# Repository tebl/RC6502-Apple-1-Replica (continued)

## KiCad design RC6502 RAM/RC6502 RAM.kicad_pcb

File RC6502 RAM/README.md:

# RC6502 RAM

The original Apple 1 computer only came with 8KB of RAM (Random Access Memory), this was divided into two separate 4KB blocks and should match the following layout (picture from Tom Owads Apple 1 Replica book):

.PNG)

The RC6502 computer makes the same changes to the hardware dealing with RAM as was details in the previously mentioned book, the updated memory map should now match the one included below (note that any optional modules are not included here). The blue areas designating RAM have shifted positions, mostly we've moved the area usually used for Integer Basic into ROM (see the [ROM](https://github.com/tebl/RC6502/tree/master/RC6502%20ROM)-module for more information). The initial version of the RAM module simply split the 64K memory space supported by the 6502 processor into two, the lower 32K being dedicated to RAM giving us the following memory layout:

.PNG)

The newly redesigned RAM module now also support ROM ICs, this can be done by jumpering WE across pins 2-3 to disable the write signal usually sent to the chip. The previous scheme of splitting the memory space into two 32K sections has been kept, the HI/LO jumper is used as to select adressing segments between $0000 through $7FFF or alternatively $8000 through $FFFF. Each 4KB section within the selected 32KB segment can then be enabled/disabled using the corresponding jumpers, this way a single board can be active within memory segments of sizes from 4KB to 32KB.

When used in combination with (E)EPROMs smaller than 32KB, such as the 27C64 or 28C64 you need to leave A13_EN and A14_EN unjumpered since those pins would be designated NC (No Connect) on the ICs themselves. Note that since ICs of this size are usually 8KB you'd only have two 4KB blocks available, enabling these in the certain combinations would lead to repetitions within the memory space. 32KB ROM chips are more than likely cheaper to obtain anyway, meaning that this would be a nice way to add more ROM-based software to the computer without much added complexity.

# Schematic
The supplied KiCad files should be sufficient as both a schematic and as a starting
point for ordering PCBs, the schematic is also available in
[PDF-format](https://github.com/tebl/RC6502-Apple-1-Replica/blob/master/RC6502%20RAM/export/RC6502%20RAM.pdf). You can refer to the BOM below for a list of suggested components to use, part numbers in parenthesis are optional and is not required.

# BOM
These are the components needed to put together your very own RAM-module for the RC6502 computer, should be able to get all of this from your favourite parts supplier through your favourite local parts supplier. For the pin headers, both male and female - if you can't find the exact pin count, just buy the longer versions and snip/cut off the parts you don't need (get extra in case of accidents, and don't cut yourself either!). Part counts in parenthesis are to be considered optional, so if you don't have any plans for them - then they can probably be left out until you need them.

| Reference | Item                                  | Count  |
| --------- | ------------------------------------- | ------ |
| PCB       | Fabricate yourself using KiCad files  |     1  |
| C1-C5     | 100nF ceramic capacitor               |     5  |
| J3        | 1x39 right angle pin header, male     |     1  |
| JP1-JP2   | 1x2 straight pin header, male         |     2  |
| JP3-JP13  | 1x3 straight pin header, male         |    10  |
| U1        | 62256 SRAM or 28C256, both DIP-28     |     1  |
| U2        | 74LS138 DIP                           |     1  |
| U3-U4     | 74LS08 DIP                            |     2  |
| U5        | 74LS00 DIP                            |     1  |
|           | Jumper caps                           | 3 (10) |

If you would like to have a copy of one or more modules, what you'll need to do is zip up the contents of the export directory for each module and give that to your favourite PCB fabrication plant. Personally I prefer to use [PCBWay](https://www.pcbway.com/setinvite.aspx?inviteid=88707), each module has been designed to fit inside the 5$ dimensions. Use the link provided when signing up to support this project!

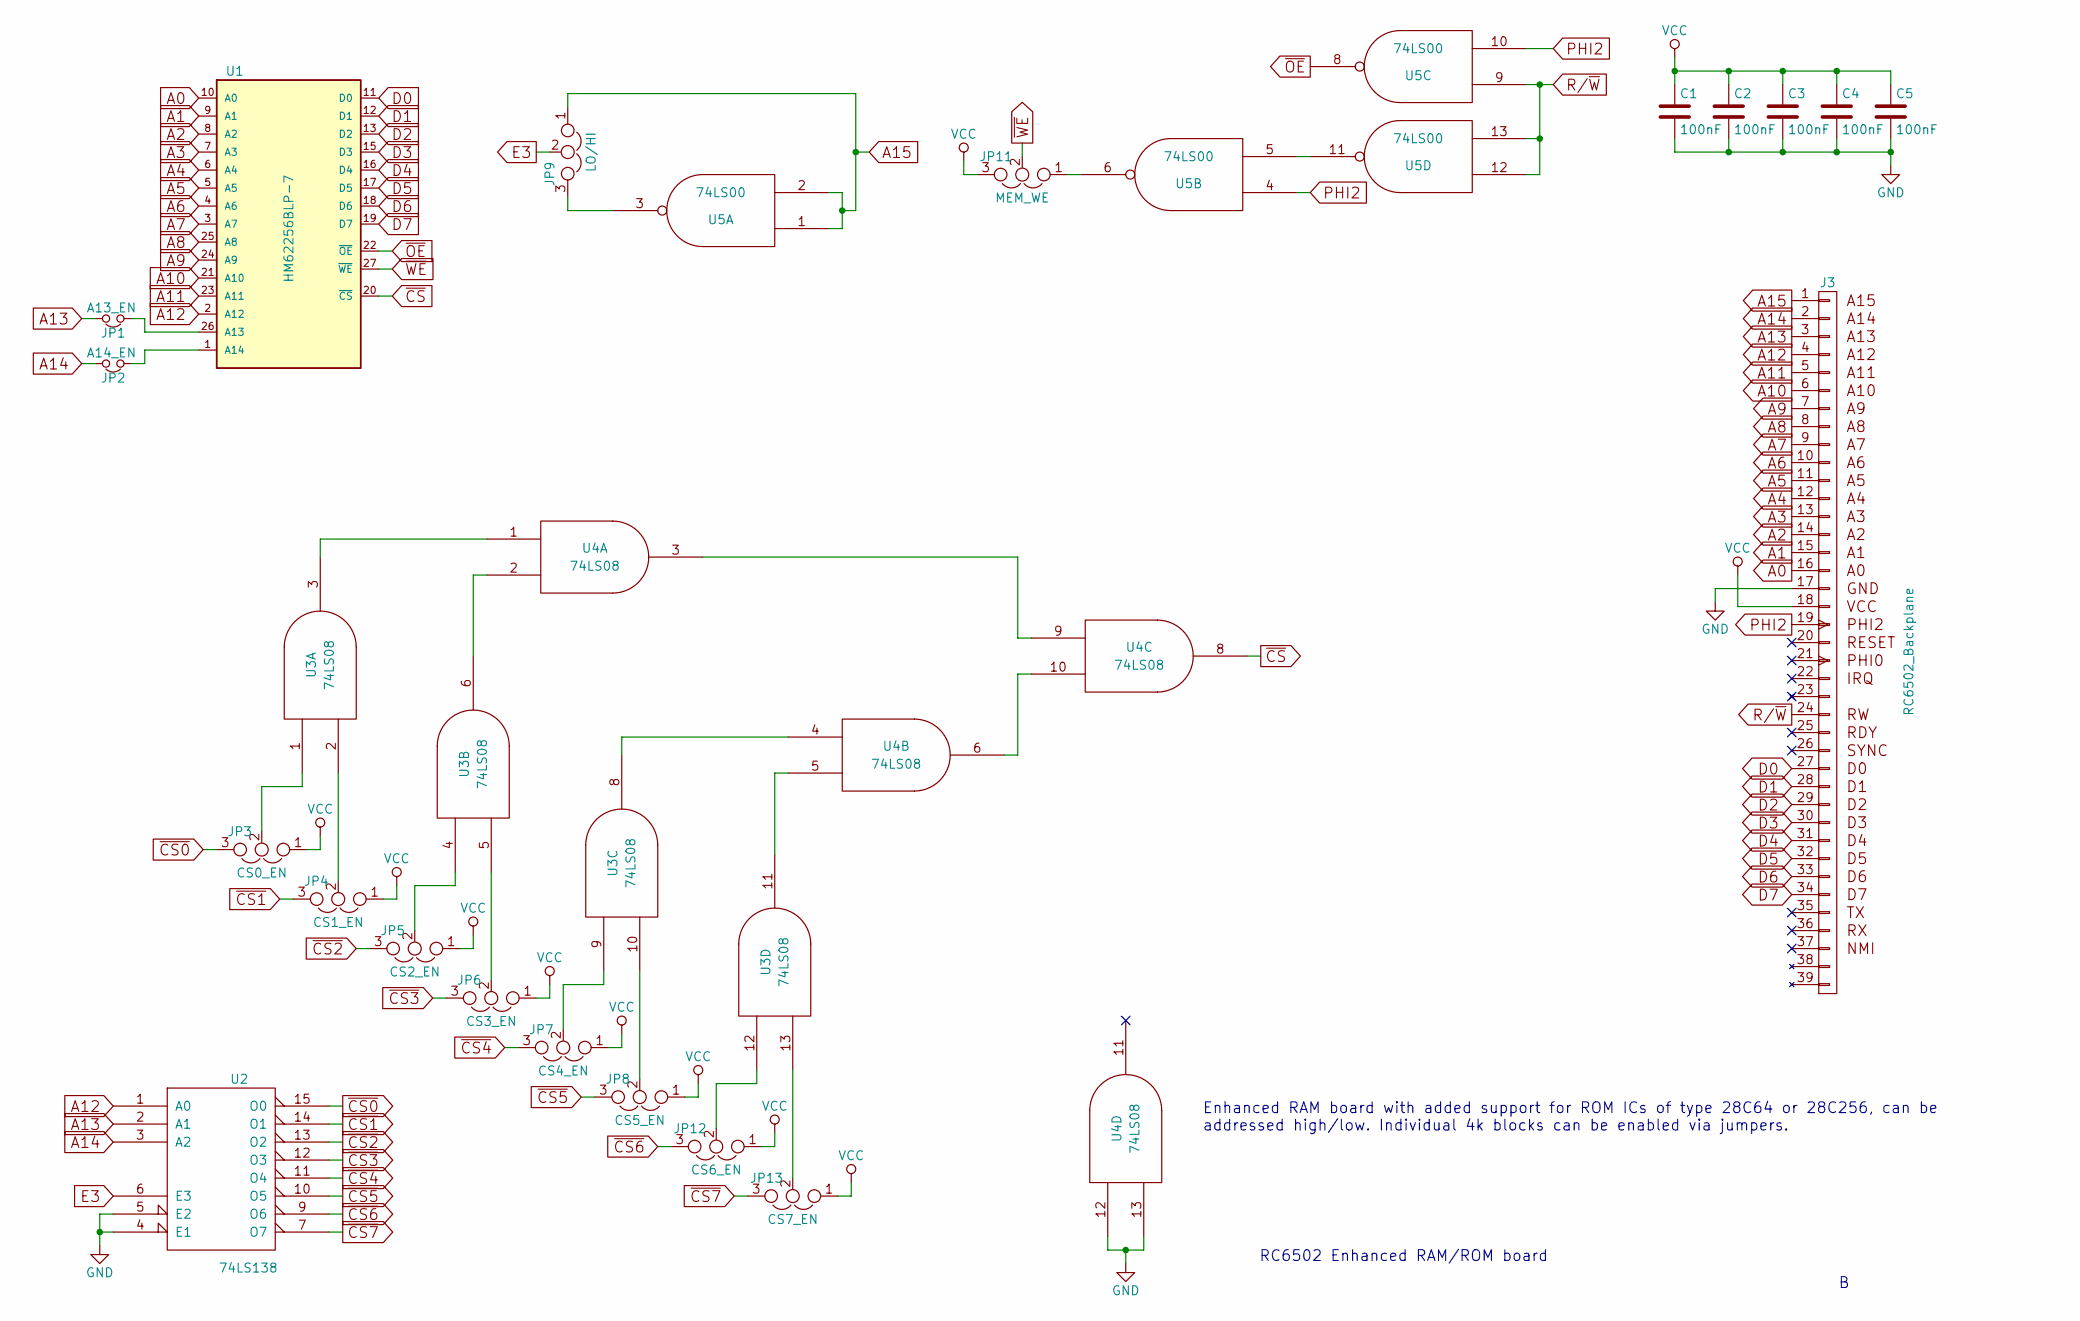
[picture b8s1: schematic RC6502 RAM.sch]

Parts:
C1, C2, C3, C4, C5: 100nF; C_Disc_D4.7mm_W2.5mm_P5.00mm
J3: RC6502_Backplane; Pin_Header_Angled_1x39_Pitch2.54mm
JP1: A13_EN; Pin_Header_Straight_1x02_Pitch2.54mm
JP2: A14_EN; Pin_Header_Straight_1x02_Pitch2.54mm
JP3: CS0_EN; Pin_Header_Straight_1x03_Pitch2.54mm
JP4: CS1_EN; Pin_Header_Straight_1x03_Pitch2.54mm
JP5: CS2_EN; Pin_Header_Straight_1x03_Pitch2.54mm
JP6: CS3_EN; Pin_Header_Straight_1x03_Pitch2.54mm
JP7: CS4_EN; Pin_Header_Straight_1x03_Pitch2.54mm
JP8: CS5_EN; Pin_Header_Straight_1x03_Pitch2.54mm
JP9: LO/HI; Pin_Header_Straight_1x03_Pitch2.54mm
JP11: MEM_WE; Pin_Header_Straight_1x03_Pitch2.54mm
JP12: CS6_EN; Pin_Header_Straight_1x03_Pitch2.54mm
JP13: CS7_EN; Pin_Header_Straight_1x03_Pitch2.54mm
U1: HM62256BLP-7; DIP-28_W15.24mm_Socket
U2: 74LS138; DIP-16_W7.62mm_Socket
U3, U4: 74LS08; DIP-14_W7.62mm_Socket
U5: 74LS00; DIP-14_W7.62mm_Socket

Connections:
A0: J3.16 (A0), U1.10 (A0)
A1: J3.15 (A1), U1.9 (A1)
A2: J3.14 (A2), U1.8 (A2)
A3: J3.13 (A3), U1.7 (A3)
A4: J3.12 (A4), U1.6 (A4)
A5: J3.11 (A5), U1.5 (A5)
A6: J3.10 (A6), U1.4 (A6)
A7: J3.9 (A7), U1.3 (A7)
A8: J3.8 (A8), U1.25 (A8)
A9: J3.7 (A9), U1.24 (A9)
A10: J3.6 (A10), U1.21 (A10)
A11: J3.5 (A11), U1.23 (A11)
A12: J3.4 (A12), U1.2 (A12), U2.1 (A0)
A13: J3.3 (A13), JP1.2, U2.2 (A1)
A14: J3.2 (A14), JP2.2, U2.3 (A2)
A15: J3.1 (A15), JP9.1, U5.1, U5.2
D0: J3.27 (D0), U1.11 (D0)
D1: J3.28 (D1), U1.12 (D1)
D2: J3.29 (D2), U1.13 (D2)
D3: J3.30 (D3), U1.15 (D3)
D4: J3.31 (D4), U1.16 (D4)
D5: J3.32 (D5), U1.17 (D5)
D6: J3.33 (D6), U1.18 (D6)
D7: J3.34 (D7), U1.19 (D7)
E3: JP9.2, U2.6 (E3)
GND: C1.2, C2.2, C3.2, C4.2, C5.2, J3.17, U1.14 (GND), U2.4 (E1), U2.5 (E2), U2.8 (GND), U3.7 (GND), U4.7 (GND), U4.12, U4.13, U5.7 (GND)
unnamed: JP1.1, U1.26 (A13)
unnamed: JP2.1, U1.1 (A14)
unnamed: JP3.2, U3.1
unnamed: JP4.2, U3.2
unnamed: JP5.2, U3.4
unnamed: JP6.2, U3.5
unnamed: JP7.2, U3.9
unnamed: JP8.2, U3.10
unnamed: JP9.3, U5.3
unnamed: JP11.1, U5.6
unnamed: JP12.2, U3.12
unnamed: JP13.2, U3.13
unnamed: U3.3, U4.1
unnamed: U3.6, U4.2
unnamed: U3.8, U4.4
unnamed: U3.11, U4.5
unnamed: U4.3, U4.9
unnamed: U4.6, U4.10
unnamed: U5.5, U5.11
PHI2: J3.19 (PHI2), U5.4, U5.10
R/~W: J3.24 (RW), U5.9, U5.12, U5.13
VCC: C1.1, C2.1, C3.1, C4.1, C5.1, J3.18, JP3.1, JP4.1, JP5.1, JP6.1, JP7.1, JP8.1, JP11.3, JP12.1, JP13.1, U1.28 (VCC), U2.16 (VCC), U3.14 (VCC), U4.14 (VCC), U5.14 (VCC)
~CS: U1.20 (~CS), U4.8
~CS0: JP3.3, U2.15 (O0)
~CS1: JP4.3, U2.14 (O1)
~CS2: JP5.3, U2.13 (O2)
~CS3: JP6.3, U2.12 (O3)
~CS4: JP7.3, U2.11 (O4)
~CS5: JP8.3, U2.10 (O5)
~CS6: JP12.3, U2.9 (O6)
~CS7: JP13.3, U2.7 (O7)
~OE: U1.22 (~OE), U5.8
~WE: JP11.2, U1.27 (~WE)

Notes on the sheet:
RC6502 Enhanced RAM/ROM board
Enhanced RAM board with added support for ROM ICs of type 28C64 or 28C256, can be addressed high/low. Individual 4k blocks can be enabled via jumpers.

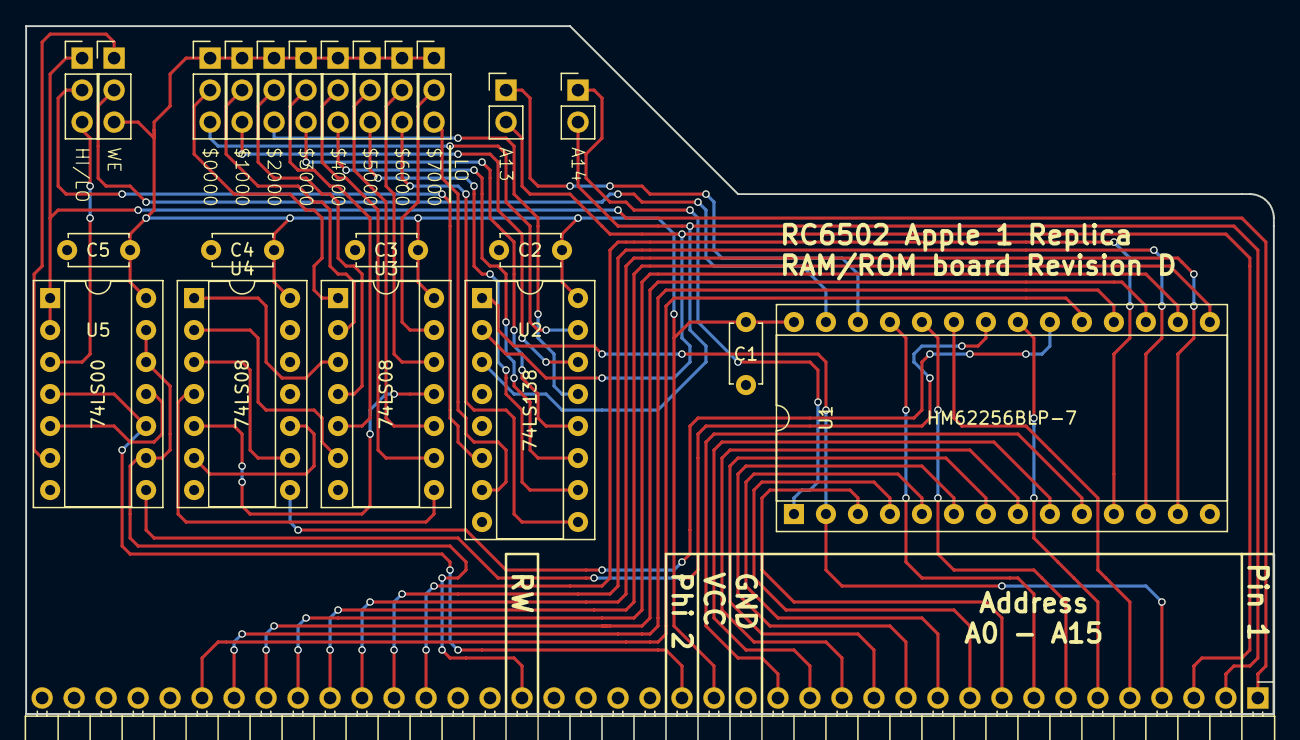
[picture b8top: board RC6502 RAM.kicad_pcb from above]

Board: 2 copper layers, 99.1 x 54.6 mm, 23 parts (0 on the bottom side), 59 nets.

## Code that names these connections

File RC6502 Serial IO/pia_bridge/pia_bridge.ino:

#include <SPI.h>
#include <MCP23S17.h>

#define DEBUG 0
#define KBD_INTERRUPT_ENABLE true
#define KBD_SEND_TIMEOUT 23

#define IO_SS 10

#define IO_VIDEO 0
#define IO_VIDEO_D0 0
#define IO_VIDEO_D6 6
#define VIDEO_RDA 5
#define VIDEO_DA 3

#define IO_KBD 1
#define IO_KBD_D0 8
#define IO_KBD_D6 14
#define IO_KBD_DA 15
#define KBD_READY 2
#define KBD_STROBE 4

MCP23S17 bridge(&SPI, IO_SS, 0);

void setup() {
  Serial.begin(115200);
  configure_pins();
  configure_bridge();
  output_status();
}

void configure_pins() {
  pinMode(KBD_READY, INPUT);
  pinMode(VIDEO_DA, INPUT);
  pinMode(KBD_STROBE, OUTPUT);
  pinMode(VIDEO_RDA, OUTPUT);
}

void configure_bridge() {
  bridge.begin();

  /* Configure video section */
  for (int i = IO_VIDEO_D0; i <= IO_VIDEO_D6; i++) {
    bridge.pinMode(i, INPUT);
  }
  bridge.pinMode(7, INPUT_PULLUP);

  /* Configure keyboard section */
  for (int i = 8; i <= 15; i++) {
    bridge.pinMode(i, OUTPUT);
  }
}

void output_status() {
  Serial.println("RC6502 Apple 1 Replica");
  
  debug_value("Video DA", digitalRead(VIDEO_DA));
  debug_value("Video D0-D6", bridge.readPort(IO_VIDEO) & 127);
  debug_value("Keyboard RDY", digitalRead(KBD_READY));
}

void debug_value(String description, byte value) {
  debug_value(description, value, 1);
}

void debug_value(String description, byte value, int level) {
  if (DEBUG < level) return;
  Serial.print(description);
  Serial.print(": ");
  print_hex(value);
}

void print_hex(byte value) {
  print_hex(value, true);
}

void print_hex(byte value, bool newline) {
  if (value <= 0xF) {
    Serial.print("0x0");
  } else {
    Serial.print("0x");
  }
  
  if (newline) Serial.println(value, HEX);
  else Serial.print(value, HEX);
}

void serial_receive() {
  if (Serial.available() > 0) {
    int c = Serial.read();
    debug_value("PIA RX", c, 10);
    pia_send(c);
  }
}

void pia_send(int c) {
  /* Make sure STROBE signal is off */
  digitalWrite(KBD_STROBE, LOW);
  c = map_to_ascii(c);

  /* Output the actual keys as long as it's supported */
  if (c < 96) {
    bridge.writePort(IO_KBD, c | 128);

    digitalWrite(KBD_STROBE, HIGH);
    if (KBD_INTERRUPT_ENABLE) {
      byte timeout;

      /* Wait for KBD_READY (CA2) to go HIGH */
      timeout = KBD_SEND_TIMEOUT;
      while(digitalRead(KBD_READY) != HIGH) {
        delay(1);
        if (timeout == 0) break;
        else timeout--;
      }
      digitalWrite(KBD_STROBE, LOW);

      /* Wait for KBD_READY (CA2) to go LOW */
      timeout = KBD_SEND_TIMEOUT;
      while(digitalRead(KBD_READY) != LOW) {
        delay(1);
        if (timeout == 0) break;
        else timeout--;
      }
    } else {
      delay(KBD_SEND_TIMEOUT);
      digitalWrite(KBD_STROBE, LOW);
    }
  }
}

char map_to_ascii(int c) {
  /* Convert ESC key */
  if (c == 203) {
    c = 27;
  }

  /* Ctrl A-Z */
  if (c > 576 && c < 603) {
    c -= 576;
  }

  /* Convert lowercase keys to UPPERCASE */
  if (c > 96 && c < 123) {
    c -= 32;
  }
  
  return c;
}

void serial_transmit() {
  digitalWrite(VIDEO_RDA, HIGH);

  if (digitalRead(VIDEO_DA) == HIGH) {
    char c = bridge.readPort(IO_VIDEO) & 127;
    debug_value("PIA TX", c, 10);
    digitalWrite(VIDEO_RDA, LOW);
    delay(12);

    send_ascii(c);
  }
}

char send_ascii(char c) {
  switch (c) {
    case 0x0d: Serial.println(); /* Replace CR with LF */
    default:
      Serial.print(c);
  }
}

void loop() {
  serial_receive();
  serial_transmit();
}

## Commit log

2017-05-14 Added files
2017-05-14 Updated net lists
2017-05-14 Added oscillator to CPU board
2017-05-15 Moved SPI breakout connector
2017-05-15 Mapped out PCB
2017-05-15 Exported files
2017-05-19 Added a couple images to gallery
2017-05-29 Added jumper select to decide if paging hardware installed
2017-05-29 Added rom files
2017-05-29 Non-functional version of serial communications
2017-05-29 Added pdf export
2017-05-30 Reorganized some code (still not working though)
2017-05-30 updated export
2017-05-30 Dump pin status on setup
2017-05-30 Exported all schematics to PDF
2017-06-01 Pullups changed to 3.3K and added VP jumper
2017-06-01 Put RDY and Sync on the bus
2017-06-01 Renamed some pins
2017-06-01 Working code.
2017-06-01 Adapted output so it works in PuTTY
2017-06-01 Use KBD interrupt to detect when computer has read character sent (Arduino doesn't support flow control in other direction)
2017-06-01 Renamed arduino sketch
2017-06-01 Moved ATTiny Clock exported files
2017-06-02 Added brackets around each byte received in debug 5.
2017-06-02 Added pictures of working setup
2017-06-02 Reformatted README, added links to each relevant module.
2017-06-05 Added Serial IO README
2017-06-07 Added BOM notice
2017-06-08 Serial IO Revision B
2017-06-08 Added Video Adapter
2017-06-08 Changed crystal footprint
2017-06-09 ROM revision B
    JP5 inside U3 footprint is used to designate wether paging hardware is installed or not (skip C3 and U3).
2017-06-09 Moved JP5 pins to back of board, only want to solder wire across it and not actually mount pins.
2017-06-09 CPU revision B
    VP pin was added for W65c02, added SYNC and RDY pins and removed hex inverter.
2017-06-10 RAM revision B
    Fixed silkscreen notes by swapping high/low text, moved around tracks to make it a little more compact.
2017-06-10 Reset circuit revision B
    Fixed floating inputs on hex inverter (needed when using HCT), added 74HCT74 in order to allow clock division by 2 and 4 (in case missing matching TTL quartz crystal or want even slower clock than st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
2017-06-10 Added SPI breakout details to silkscreen
2017-06-11 Hide diode name (only one anyways)
2017-06-11 Video Adapter revision B
    Adds IO expanders for possibly offloading the actual image output rendering to an analog module via a separate connector.
2017-06-11 Fixed video adapter rca connector footprint.
2017-06-11 Exported pcb preview
2017-06-13 Updated README.
2017-06-13 typo :(
2017-06-15 Connected RDY to the wrong pin. Ooops!
2017-06-15 Created simple backplane connector template
    Need to use this since KiCAD seems unable to copy between sheets.
2017-06-15 Updated Gerber exports before sending to manufacturing
2017-06-15 SBC PCB layout completed
2017-06-15 Added ROM reference to SBC
2017-06-15 Added silkscreen newbie hints.
2017-06-15 Added VP GND details to silkscreen.
2017-06-16 Added all components
2017-06-17 Yeah, I'm not going to get this within 10x10cm :-(
2017-06-17 Exported files with updated silkscreen
2017-06-19 Updated exports before sending to fabrication.
2017-07-09 SBC Revision B
    Revision A still don't work with W65c02 processors, added BE signal pull-up (untested wether this improves 65c02 compatibility).
2017-07-12 Moved oscillator right way up.
2017-11-10 Updated export and added screenshots
2018-03-10 SBC README added
2018-03-10 R10 notice added
2018-03-10 Added README image
2018-03-10 Added Arduino Nano to BOM
2018-03-10 Updated main README to mention SBC version
2018-03-10 Show R10, don't just link it!
2018-12-02 VDU basic IO mapping start
2018-12-04 Initial simulation of chip selects
2018-12-04 Digital logic added to schematic
2018-12-04 Added analog circuit
2018-12-04 Added description
2018-12-04 Assigned footprints
2018-12-04 Fixed footprint error
2018-12-04 Forced KiCad to actually use GND as ground name
2018-12-19 Moved incomplete add-on cards to abandoned.
2018-12-21 Schematic done for enhanced RAM/ROM board
2018-12-22 Enhanced RAM/ROM board, routing done
2018-12-23 Flipped decoder inputs, added details to silkscreen.
2018-12-23 Added schematic for a bus monitor and single stepping card.
2018-12-25 Exported schematic to pdf
2018-12-26 PSG sound card schematic added
2018-12-28 PSG sound card layout
2018-12-28 PSG gerber export
2018-12-29 Changed VDU CS logic ins schematic
2018-12-29 Assigned new footprints
2018-12-30 VDU PCB layout done
2018-12-30 Cleaned up silkscreen
2018-12-30 Tried to increase ground plane flow
2018-12-31 Exported gerber files for VDU
2019-01-02 SBC uses new oscillator footprint
2019-01-04 Added backplane schematic
2019-01-07 Backplane layout done
2019-01-07 Backplane gerber export
2019-01-12 VDU amplifier schematic done
2019-01-12 VDU amplifier layout done
2019-01-13 Added resistor values to SBC silkscreen
2019-01-13 Added ROM enable jumper to SBC
2019-01-13 Added RAM enable jumper to SBC
2019-01-14 Changed schematic symbol for capacitor on serial output line
2019-01-14 Renamed ROM file extensions to bin to reflect content
2019-01-14 Updated SBC README
2019-01-14 Updated Serial IO README
2019-01-14 Fixed typo, added BOM notes.
2019-01-14 Added memory maps
2019-01-14 Added ROM README
2019-01-14 Added ROM notice to get new RAM module instead
2019-01-14 Added CPU README
2019-01-14 Added reset circuit README
2019-01-14 Added picture note, used gallery image is from previous revision.
2019-01-14 Added backplane README
2019-01-14 Fixed typo
2019-01-14 Added RAM README
2019-02-09 Added serial adapter schematic based on 6551
2019-02-09 Added PIA enable jumper to SBC
2019-02-09 Added oscillator enable jumper to SBC
2019-02-09 Added prototyping module
2019-02-11 Added joystick and digital I/O module
2019-02-11 Gerber export
2019-02-11 Added bleed LED to backplane
2019-02-12 Added TIA module schematic
2019-02-12 TIA layout done
2019-02-13 Moved CADJ potentiometer
2019-02-13 Silkscreen details added
2019-02-13 Renamed P to analog to match RIOT
2019-02-13 Added RIOT module schematic
2019-02-14 RIOT module layout done
2019-02-14 Updated gerbers for order
2019-02-16 Fixed RAM board block select logic
2019-02-16 Updated RAM board BOM
2019-02-20 Updated VDU schematic with rev. B fixes
2019-02-20 Updated layout to include changes
2019-02-20 Added VDU Color Amplifier based on MC1372
2019-02-20 Minor SBC silkscreen tweaks
2019-02-20 PSG usage notes (still not working)
2019-02-20 Added silkscreen markings for AUX header
2019-02-24 SBC revision E was missing VCC to CPU for some reason
2019-02-27 VDU silkscreen tweaks
2019-02-27 Forgot to actually power amplifier circuit :-(
2019-02-28 Added TIA test ROMs
    These are from the example projects on 8bitworkshop.com for the Atari 2600.
2019-02-28 Added gallery images
2019-02-28 Added SBC readme update regarding fixes to rev D/E.
2019-03-03 Accidentally put 74LS373 instead of 74LS374
2019-03-08 TIA (NTSC) clock schematic added
2019-06-23 Revised PSG module
2019-06-23 Added Phi1 to backplane connector
2019-06-24 Debug module schematic reworked
2019-06-24 Updated backplane footprint to include phi1
2019-06-26 Updated module list
2020-01-11 RC6502 Apple 1 SBC/README: Fix spelling errors and typos
2020-01-20 Terminal board schematic
2020-01-21 Added LEDs
2020-01-21 Commit PSG changes from last year
2020-01-21 Cleaned up SBC schematic
2020-01-21 Cleaned up SBC schematic some more
2020-01-21 Terminal silkscreen got striped
2020-01-21 Memory map
2020-01-21 Moved files around
2020-01-22 Terminal gerber export
2020-01-22 Tweaked silkscreen
2020-01-22 Removed non-sensical file
2020-01-25 SBC board cleaned up and exported
2020-01-25 Serial adapter abandoned (moved to RC-ONE and completed)
2020-01-25 wozmon source
2020-02-17 Added MCP23S17 library to PlatformIO project
2020-05-19 Bus: Pinout and a little description of RC6502 bus
2020-05-19 README: Link to the Bus document
2020-05-19 Bus: Document which boards use which bus lines
2020-05-20 FIXUP SBC/README: Correct RAM/ROM enable descriptions.
2020-05-20 SBC/README: Add description of jumper settings
2020-05-24 Bus: Add comparision with RC2014 bus
    The backplanes (though not the cards) are actually fairly compatible,
    so we include this information to give guidance on using a backplane
    from one system with the other.
    This may also provide helpful insight for RC6502 board designers.
2020-05-24 Bus: Address decode mods from third party developer appleii6502
2020-12-19 PIA Communicator/platformio.ini: Fix deprecated warning on lib_extra_dirs/env and add default baudrate (monitor_speed)
    - Addresses warning on build: `lib_extra_dirs` configuration option is deprecated in section [platformio]! Please move it to global `env` section.
    - Sets default baud-rate on PlatformIO Serial Monitor.
2021-04-02 Fix SBC order link
2021-06-03 Update BOM table, PCB link, and jumper settings
    Added a variety of additional information and fixups, to the BOM table especially:
    * added some missing jumpers (JP1/J11/A13_W/A14_w)
    * jumpers were unclear outside of KiCad, added "silkscreen" column with notes
    * also added a "socket" column for parts if want to buy narrow/wide holder for any chips
    * some jumpers incorrectly had "right angle" listed where straight header needed
    * the PCBWay link was broken, updated to revH
2021-12-07 SBC/README: Fix backwards description of the VP GND jumper
    Issue #29 from ea4eoz noted that this is backwards for the revision H
    board. It's clearly must be backwards for _every_ revision, since
    closing a jumper, rather than opening it, is the way to connect the
    other side of the jumper to ground.
    (This error was inserted by me when I originally wrote this section
    of the documentation.)
2021-12-07 SBC/README: RAM_EN jumper is vertical on newer versions of the board
    Issue #29 from ea4eoz noted this, and I've confirmed myself that the latest
    revision as of this commit (e395f27) has moved the jumper to a vertical
    orientation with the lowest pin connected to Vcc.
2022-04-11 Some unfinished parts of terminal software
